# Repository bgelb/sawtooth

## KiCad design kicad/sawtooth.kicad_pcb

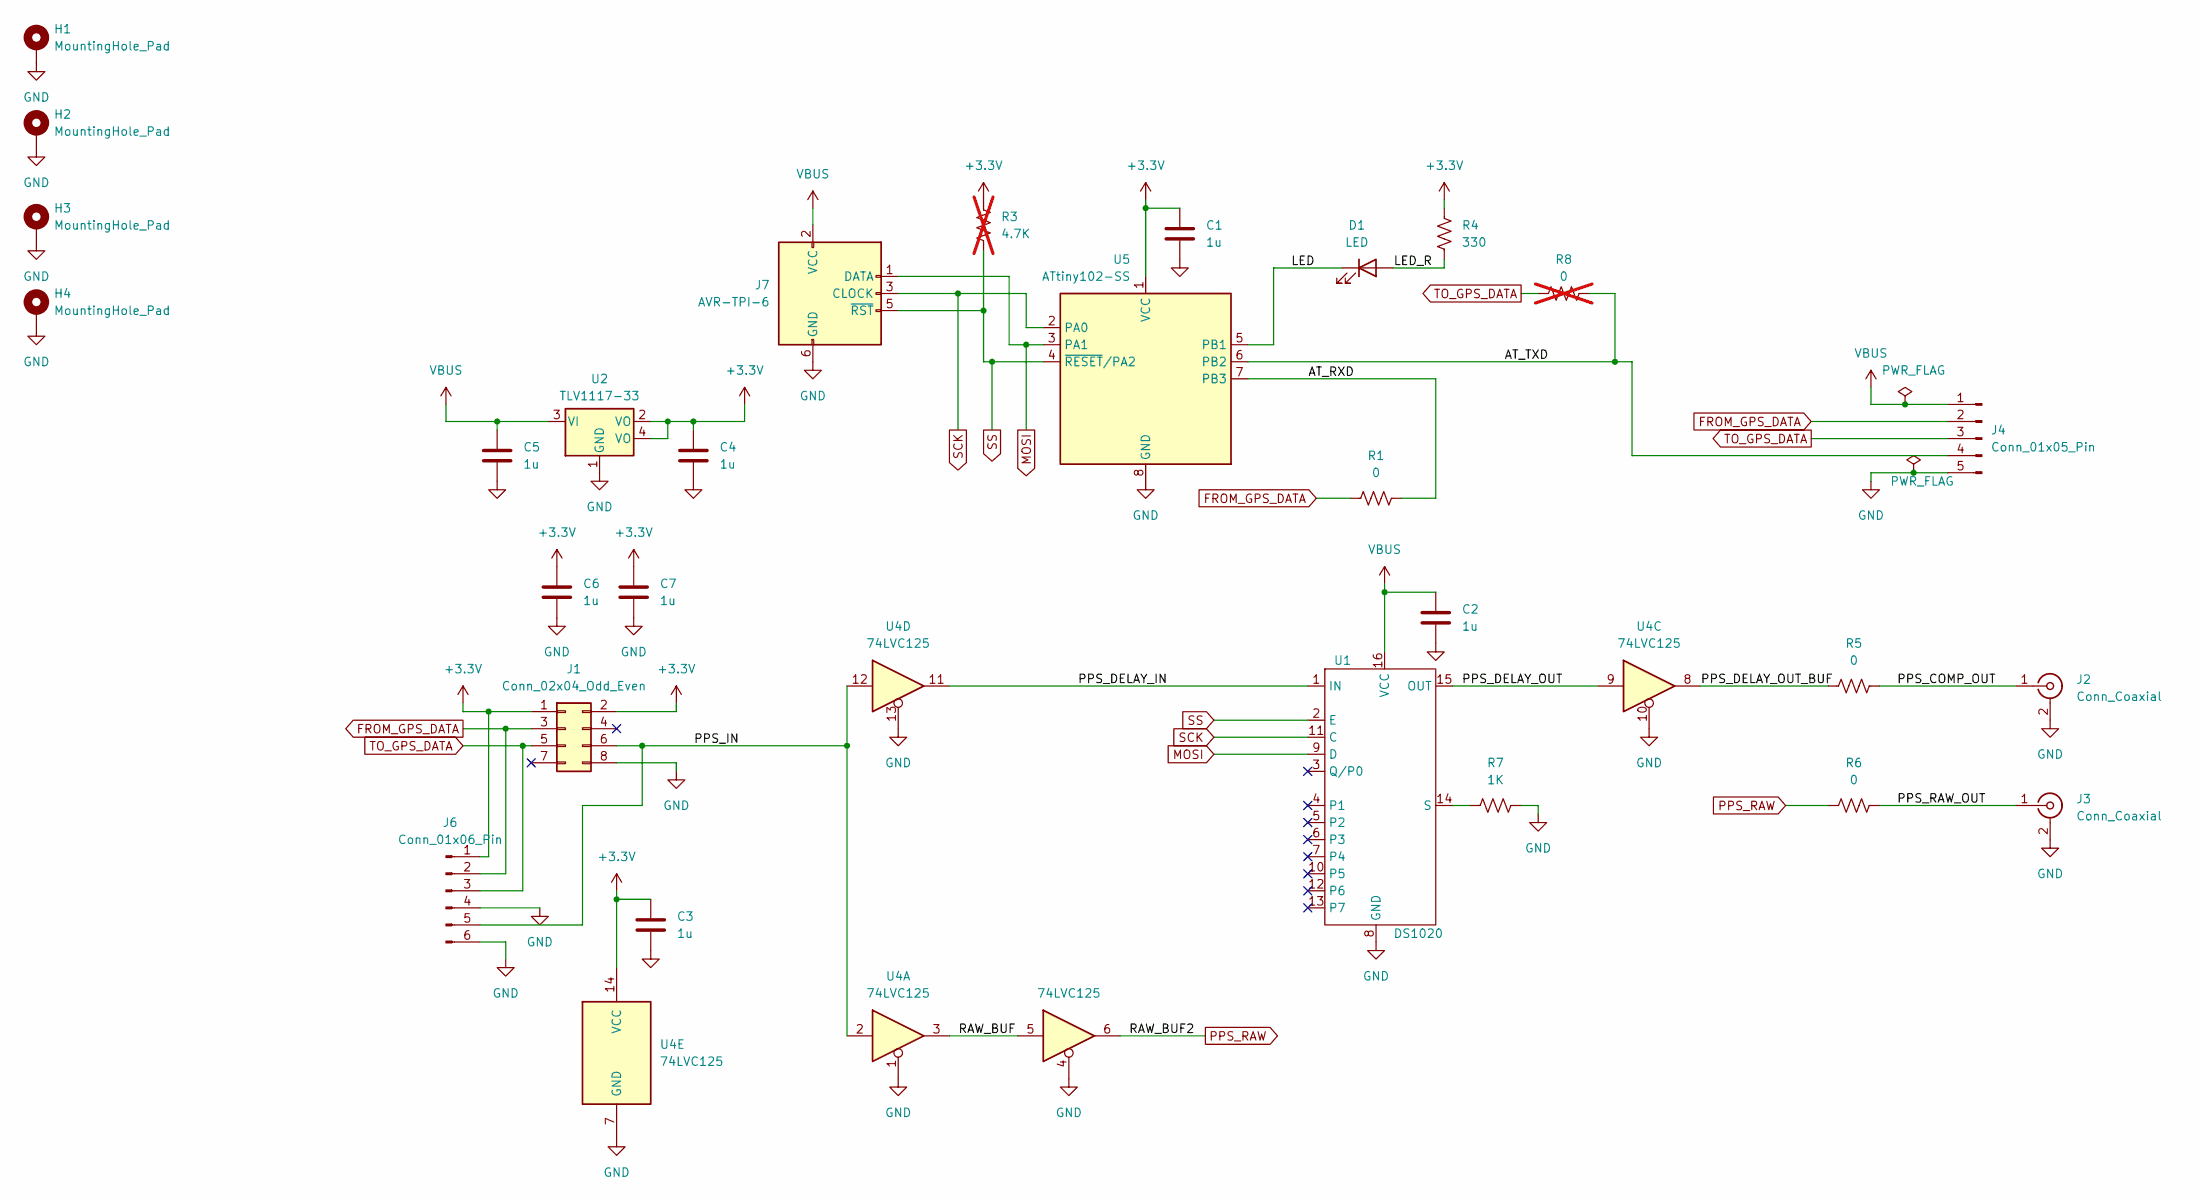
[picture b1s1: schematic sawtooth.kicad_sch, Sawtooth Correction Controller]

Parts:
C1, C2, C3, C4, C5, C6, C7: 1u; C_0805_2012Metric_Pad1.18x1.45mm_HandSolder
D1: LED; LED_1206_3216Metric_Pad1.42x1.75mm_HandSolder
H1, H2, H3, H4: MountingHole_Pad; MountingHole_3mm_Pad_TopBottom
J1: Conn_02x04_Odd_Even; PinSocket_2x04_P1.00mm_Vertical_SMD
J2, J3: Conn_Coaxial; SMA_Amphenol_901-143_Horizontal
J4: Conn_01x05_Pin; PinHeader_1x05_P2.54mm_Vertical
J6: Conn_01x06_Pin; PinHeader_1x06_P2.54mm_Vertical
J7: AVR-TPI-6; PinHeader_2x03_P2.54mm_Vertical
R1, R5, R6: 0; R_0805_2012Metric_Pad1.20x1.40mm_HandSolder
R3: 4.7K; R_0805_2012Metric_Pad1.20x1.40mm_HandSolder; not fitted
R4: 330; R_0805_2012Metric_Pad1.20x1.40mm_HandSolder
R7: 1K; R_0805_2012Metric_Pad1.20x1.40mm_HandSolder
R8: 0; R_0805_2012Metric_Pad1.20x1.40mm_HandSolder; not fitted
U1: DS1020; SOIC-16W_7.5x10.3mm_P1.27mm
U2: TLV1117-33; SOT-223
U4: 74LVC125; SOIC-14_3.9x8.7mm_P1.27mm
U5: ATtiny102-SS; SOIC-8_3.9x4.9mm_P1.27mm

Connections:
+3.3V: C1.1, C3.1, C4.1, C6.1, C7.1, J1.1, J1.2, J6.1, R3.2, R4.2, U2.2 (VO), U2.4 (VO), U4.14 (VCC), U5.1 (VCC)
/AT_RXD: R1.1, U5.7 (PB3)
/AT_TXD: J4.4, R8.1, U5.6 (PB2)
/LED: D1.1 (K), U5.5 (PB1)
/LED_R: D1.2 (A), R4.1
/PPS_COMP_OUT: J2.1 (In), R5.1
/PPS_DELAY_IN: U1.1 (IN), U4.11
/PPS_DELAY_OUT: U1.15 (OUT), U4.9
/PPS_DELAY_OUT_BUF: R5.2, U4.8
/PPS_IN: J1.6, J6.5, U4.2, U4.12
/PPS_RAW_OUT: J3.1 (In), R6.1
/RAW_BUF: U4.3, U4.5
FROM_GPS_DATA: J1.3, J4.2, J6.2, R1.2
GND: C1.2, C2.2, C3.2, C4.2, C5.2, C6.2, C7.2, H1.1, H2.1, H3.1, H4.1, J1.8, J2.2 (Ext), J3.2 (Ext), J4.5, J6.4, J6.6, J7.6 (GND), R7.1, U1.8 (GND), U2.1 (GND), U4.1, U4.4, U4.7 (GND), U4.10, U4.13, U5.8 (GND)
MOSI: J7.1 (DATA), U1.9 (D), U5.3 (PA1)
unnamed: R7.2, U1.14 (S)
PPS_RAW: R6.2, U4.6
SCK: J7.3 (CLOCK), U1.11 (C), U5.2 (PA0)
SS: J7.5 (~RST), R3.1, U1.2 (E), U5.4 (~RESET/PA2)
TO_GPS_DATA: J1.5, J4.3, J6.3, R8.2
VBUS: C2.1, C5.1, J4.1, J7.2 (VCC), U1.16 (VCC), U2.3 (VI)

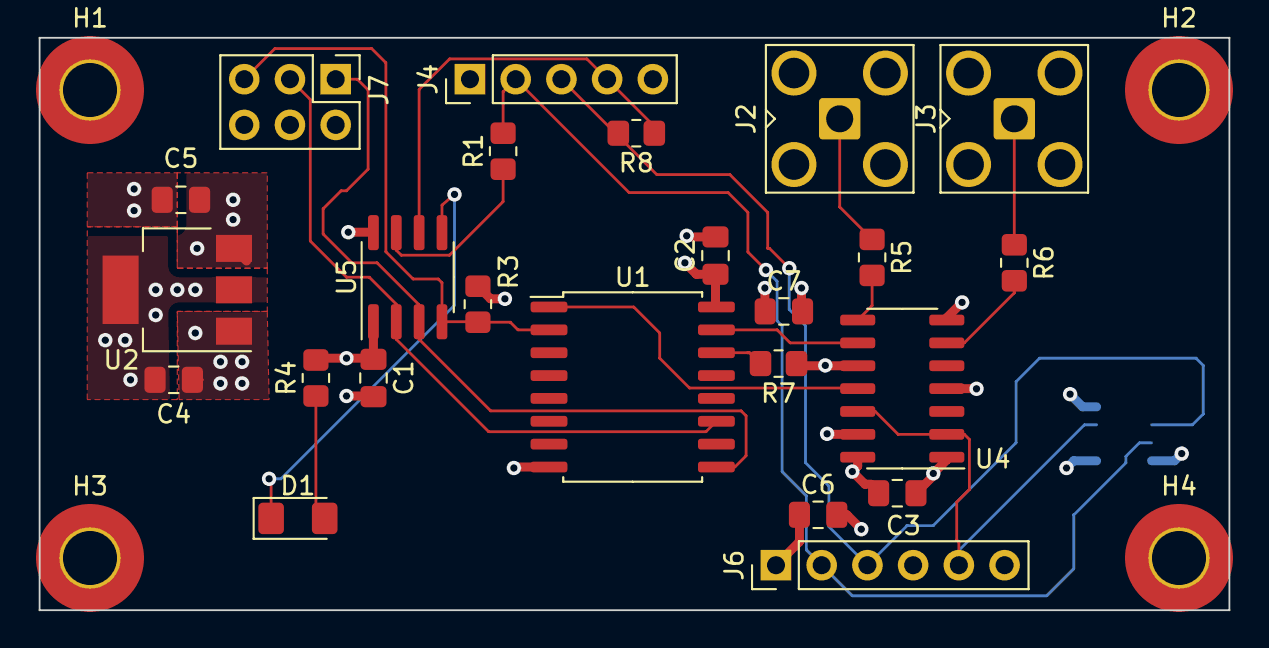
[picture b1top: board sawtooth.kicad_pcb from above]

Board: 4 copper layers, 66.1 x 31.8 mm, 29 parts (1 on the bottom side), 21 nets.

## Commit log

2024-02-16 first checkin
2024-02-16 add kicad subdir
2024-02-17 update and board start
2024-02-18 board layout done
2024-03-05 passthru on micro
2024-03-08 basic fsm working
2024-03-08 use official atmel lib
2024-03-08 checksumming
2024-03-08 spi coded
2024-03-09 woks!
2024-03-09 disable debugging
